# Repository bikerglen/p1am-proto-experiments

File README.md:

# p1am-proto-experiments
Various board and libraries to fit the Automation Direct P1AM-PROTO enclosure.
Everything here is untested. Use at your own risk. I'll accept pull requests with any corrections or other contributions.

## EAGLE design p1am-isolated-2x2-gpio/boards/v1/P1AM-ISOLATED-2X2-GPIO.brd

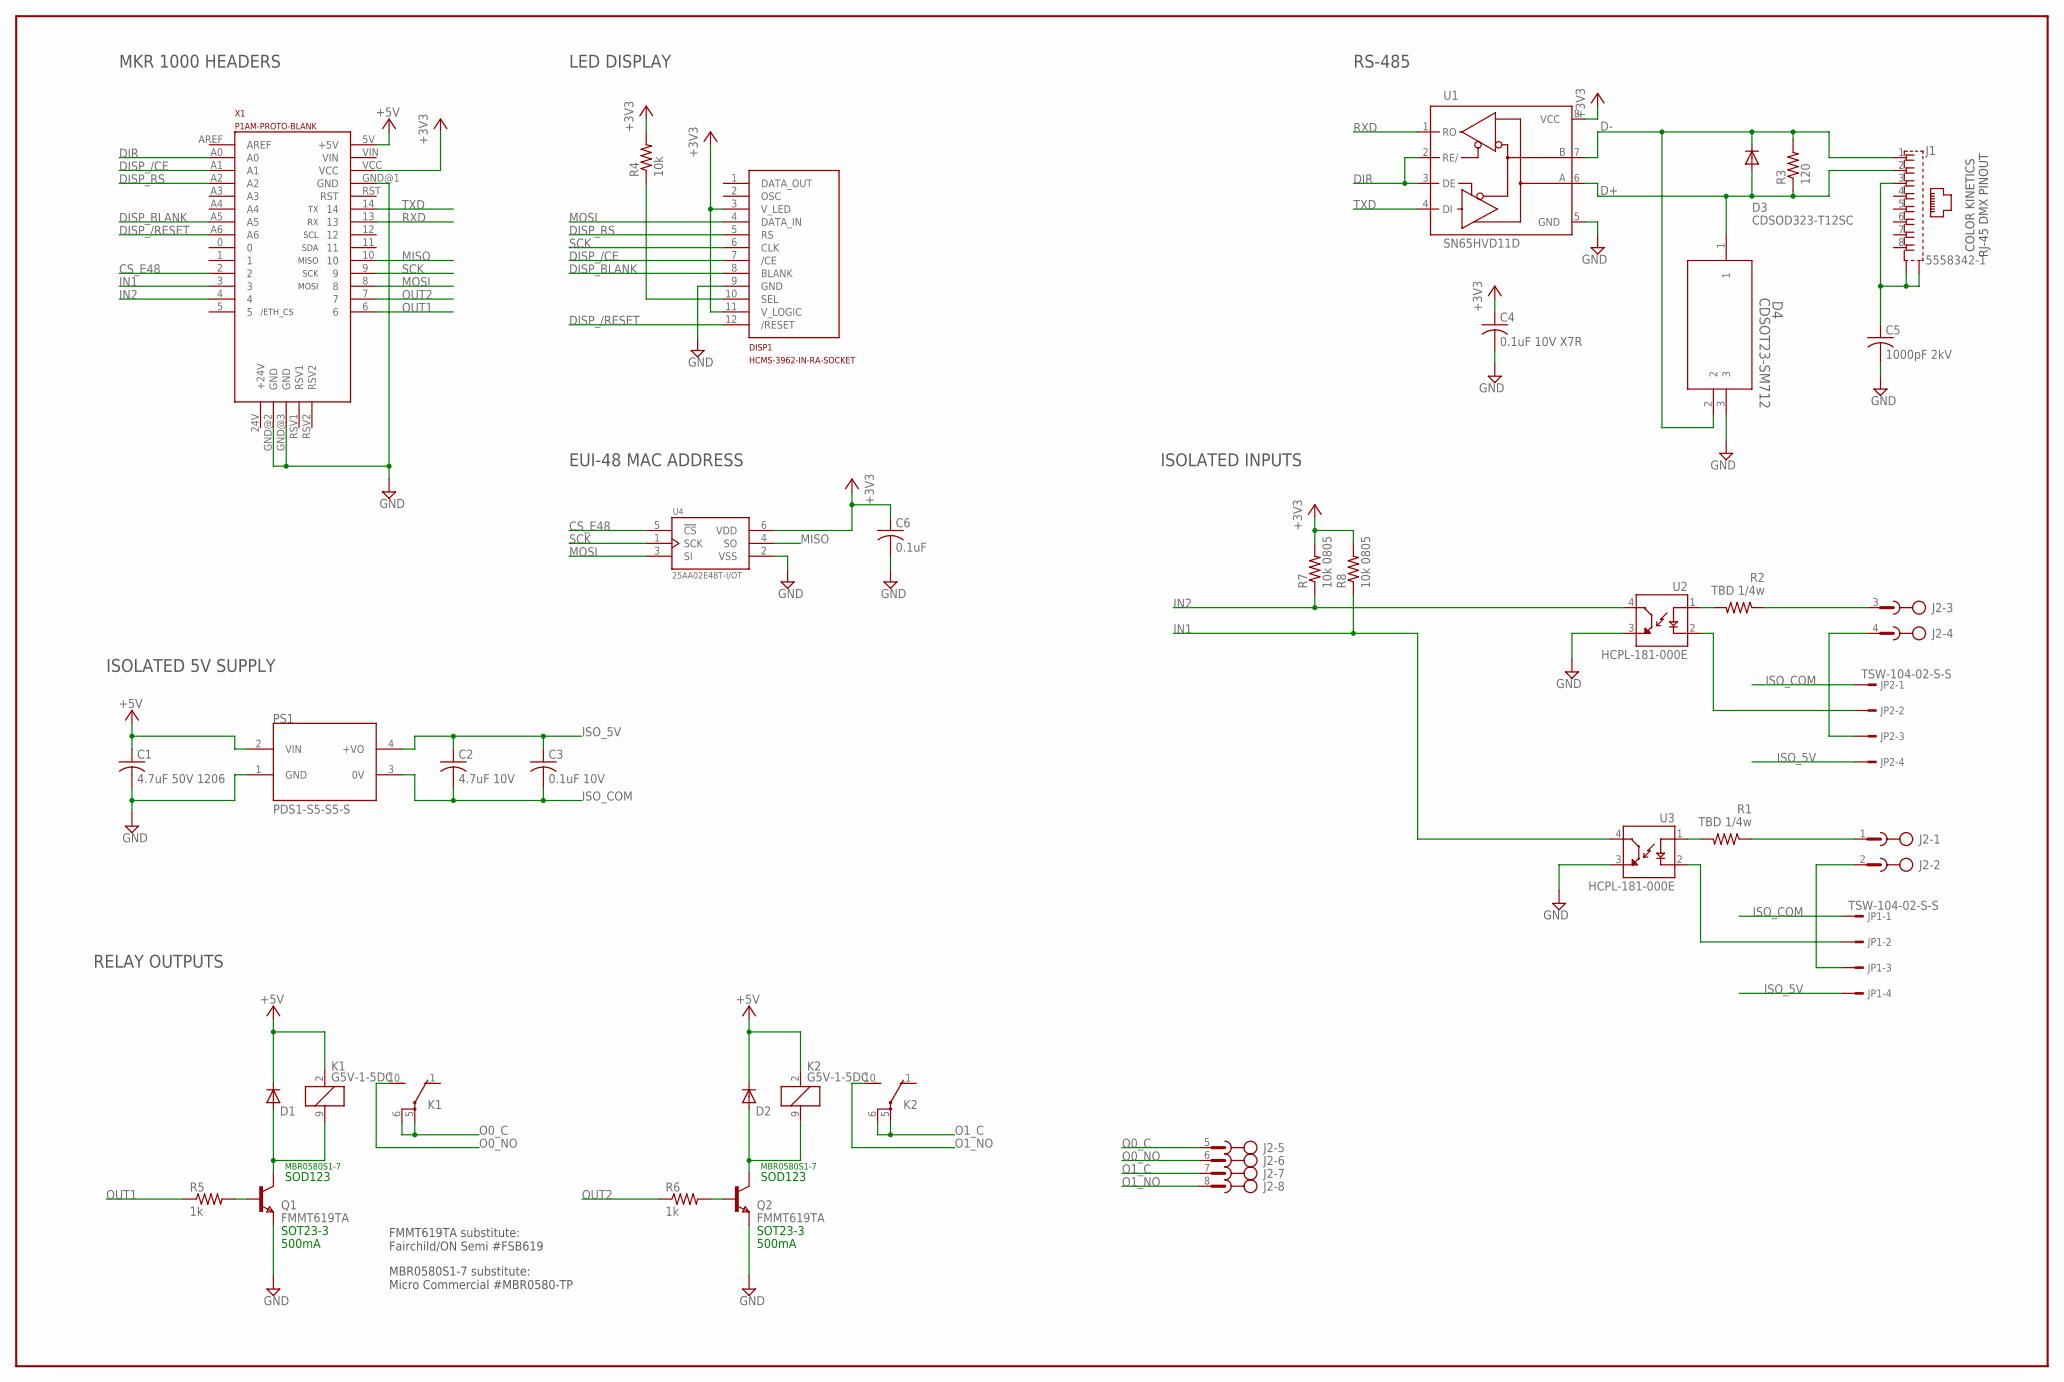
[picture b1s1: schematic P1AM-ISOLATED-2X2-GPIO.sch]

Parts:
C1: 4.7uF 50V 1206; C1206K; MFR_PART_NO C1206C475K5RACTU
C2: 4.7uF 10V; C1206K
C3: 0.1uF 10V; C1206K; MFR_PART_NO C1206C475K5RACTU
C4: 0.1uF 10V X7R; C0805
C5: 1000pF 2kV; C1206K
C6: 0.1uF; C0603
D1, D2: 1N4148W-TP; SOD123; MFR_PART_NO MBR0580S1-7
D3: CDSOD323-T12SC; SOD323-W
D4: CDSOT23-SM712; SOT_SM712
DISP1: HCMS-3962-IN-RA-SOCKET; 299-43-312-11-001000
J1: 5558342-1; TE_5558342-1
J2: PHOENIX-XXXXXXX-TERM-BLOCK-HDR-8POS-90DEG-3.5MM
JP1, JP2: TSW-104-02-S-S
K1, K2: G5V-1-5DC; G5V1; MFR_PART_NO G5V-1-DC5
PS1: PDS1-S5-S5-S; CONV_PDS1-S5-S5-S
Q1, Q2: FMMT619TA; SOT-23; MFR_PART_NO FMMT619TA
R1, R2: TBD 1/4w; R1206
R3: 120; R0805
R4: 10k; R0805
R5, R6: 1k; R1206; MFR_PART_NO CR1206-JW-102ELF
R7, R8: 10k 0805; R0805
U1: SN65HVD11D; SO08
U2, U3: HCPL-181-000E; SOIC254P675X240-4N
U4: 25AA02E48T-I/OT; SOT95P270X145-6N
X1: P1AM-PROTO-BLANK

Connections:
+3V3: C4.1, C6.1, DISP1.3 (V_LED), DISP1.11 (V_LOGIC), R4.2, R7.2, R8.2, U1.8 (VCC), U4.6 (VDD), X1.VCC
+5V: C1.1, D1.C, D2.C, K1.2 (1), K2.2 (1), PS1.2 (VIN), X1.5V (+5V)
CS_E48: U4.5 (!CS), X1.2
D+: D3.A, D4.1, J1.2, R3.1, U1.6 (A)
D-: D3.C, D4.2, J1.1, R3.2, U1.7 (B)
DIR: U1.2 (RE/), U1.3 (DE), X1.A0
DISP_/CE: DISP1.7 (/CE), X1.A1
DISP_/RESET: DISP1.12 (/RESET), X1.A6
DISP_BLANK: DISP1.8 (BLANK), X1.A5
DISP_RS: DISP1.5 (RS), X1.A2
GND: C1.2, C4.2, C5.2, C6.2, D4.3, DISP1.9 (GND), PS1.1 (GND), Q1.2 (E), Q2.2 (E), U1.5 (GND), U2.3 (EMITTER), U3.3 (EMITTER), U4.2 (VSS), X1.GND@1 (GND), X1.GND@2 (GND), X1.GND@3 (GND)
IN1: R8.1, U3.4 (COLLECTOR), X1.3
IN2: R7.1, U2.4 (COLLECTOR), X1.4
ISO_5V: C2.1, C3.1, JP1.4, JP2.4, PS1.4 (+VO)
ISO_COM: C2.2, C3.2, JP1.1, JP2.1, PS1.3 (0V)
MISO: U4.4 (SO), X1.10
MOSI: DISP1.4 (DATA_IN), U4.3 (SI), X1.8
unnamed: R1.2, U3.1 (ANODE)
unnamed: JP1.2, U3.2 (CATHODE)
unnamed: Q2.3 (B), R6.2
unnamed: D2.A, K2.9 (2), Q2.1 (C)
unnamed: J2.3, R2.1
unnamed: J2.2, JP1.3
unnamed: R2.2, U2.1 (ANODE)
unnamed: JP2.2, U2.2 (CATHODE)
unnamed: J2.1, R1.1
unnamed: J2.4, JP2.3
unnamed: C5.1, J1.3, J1.SH1 (S1), J1.SH2 (S2)
unnamed: DISP1.10 (SEL), R4.1
unnamed: Q1.3 (B), R5.2
unnamed: D1.A, K1.9 (2), Q1.1 (C)
O0_C: J2.5, K1.5, K1.6
O0_NO: J2.6, K1.10 (S)
O1_C: J2.7, K2.5, K2.6
O1_NO: J2.8, K2.10 (S)
OUT1: R5.1, X1.6
OUT2: R6.1, X1.7
RXD: U1.1 (RO), X1.13
SCK: DISP1.6 (CLK), U4.1 (SCK), X1.9
TXD: U1.4 (DI), X1.14

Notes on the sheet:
SOD123
SOT23-3
500mA
MBR0580S1-7
FMMT619TA substitute: Fairchild/ON Semi #FSB619
MBR0580S1-7 substitute: Micro Commercial #MBR0580-TP
COLOR KINETICS RJ-45 DMX PINOUT
SCL
SDA
MISO
MOSI
SCK
/ETH_CS
RS-485
ISOLATED INPUTS
RELAY OUTPUTS
MKR 1000 HEADERS
LED DISPLAY
EUI-48 MAC ADDRESS
ISOLATED 5V SUPPLY

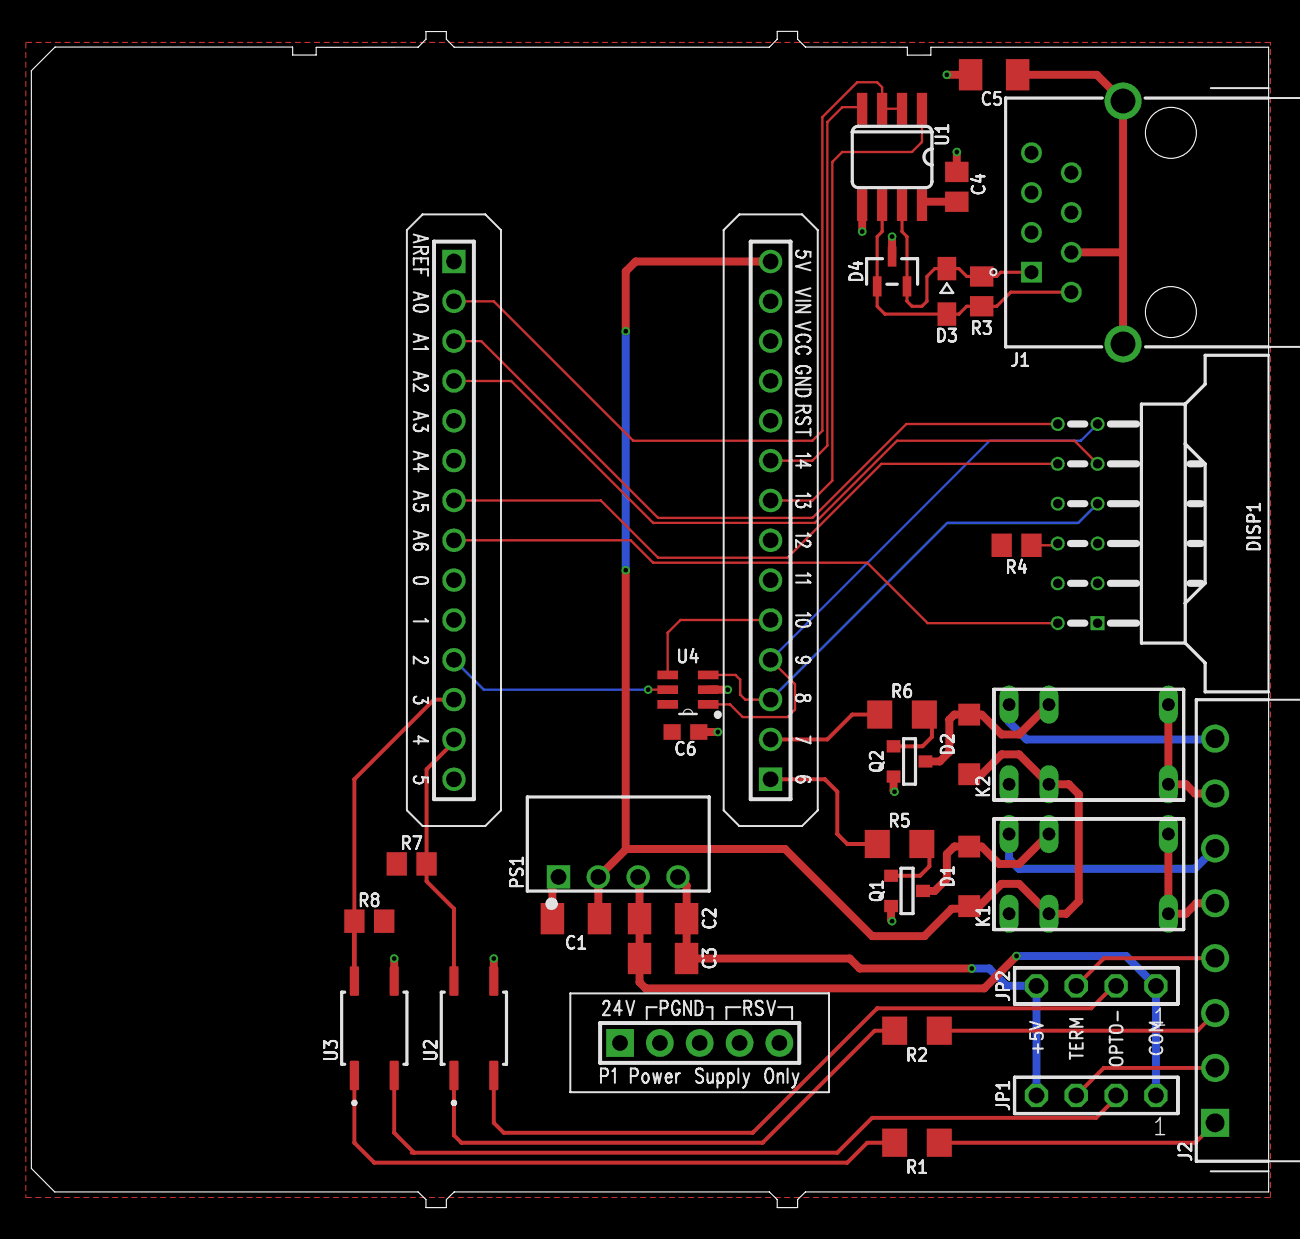
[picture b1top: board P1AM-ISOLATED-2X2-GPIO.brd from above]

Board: 2 copper layers, 78.9 x 75.0 mm, 33 parts (0 on the bottom side), 40 nets.

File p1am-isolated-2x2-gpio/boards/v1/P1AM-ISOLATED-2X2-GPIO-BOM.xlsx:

Qty | Ref | Description | Package | Mfr | Mfr Part # | Supplier | Supplier Part #
2 | C1, C2 | CAP CER 4.7UF 16V X7R 1206 | 1206 | Kemet | C1206C475K4RACTU | Digi-Key | 399-3524-1-ND
1 | C3 | CAP CER 0.1UF 16V X7R 1206 | 1206 | Kemet | C1206C104K4RACTU | Digi-Key | 399-9305-1-ND
1 | C4 | CAP CER 0.1UF 10V X7R 0805 | 0805 | Kemet | C0805C104K8RACTU | Digi-Key | 399-7999-1-ND
1 | C5 | CAP CER 1000pF 2KV 10% X7R SMD 1206 | 1206 | Johanson Dielectrics | 202R18W102KV4E | Digi-Key | 709-1036-1-ND
1 | C6 | CAP CER 0.1UF 50V X7R 0603 | 0603 | Kemet | C0603C104K5RACTU | Digi-Key | 399-5089-1-ND
2 | D1, D2 | DIODE GEN PURP 100V 150MA SOD123 | SOD123 | Micro Commercial Co | 1N4148W-TP | Digi-Key | 1N4148WTPMSCT-ND
1 | D3 | TVS DIODE 12V 29.5V SOD323 | SOD323 | Bourns Inc. | CDSOD323-T12SC | Digi-Key | CDSOD323-T12SCCT-ND
1 | D4 | TVS DIODE 7V/12V 14V/26V SOT23-3 | SOT23 | Bourns Inc. | CDSOT23-SM712 | Digi-Key | CDSOT23-SM712CT-ND
1 | DISP1-DISPLAY | LED DISPLAY 5X7 4CHAR 5MM RED | --- | Broadcom | HCMS-3962 | Digi-Key | 516-3920-ND
1 | DISP1-SOCKET | CONN IC DIP SOCKET 12POS GOLD | --- | Mill-Max | 299-43-312-11-001000 | Digi-Key | ED90160-ND
1 | J1 | CONN MOD JACK 8P8C R/A SHIELDED | 8P8C | TE Connectivity | 5558342-1 | Digi-Key | A31466-ND
1 | J2-HEADER | TERM BLOCK HDR 8POS 90DEG 3.5MM | --- | Würth Elektronik | 691322110008 | Digi-Key | 732-2774-ND
1 | J2-PLUG | TERM BLOCK PLUG 8POS STR 3.5MM | --- | Würth Elektronik | 691361100008 | Digi-Key | 732-2756-ND
2 | JP1, JP2 | CONN HEADER VERT 4POS 2.54MM | --- | Samtec | TSW-104-07-G-S | Digi-Key | SAM1029-04-ND
2 | K1, K2 | RELAY GEN PURPOSE SPDT 1A 5VDC | --- | Omron | G5V-1-DC5 | Digi-Key | Z773-ND
1 | PS1 | DC DC CONVERTER 5V 1W | --- | Cui | PDS1-S5-S5-S | Digi-Key | 102-2758-ND
2 | Q1, Q2 | TRANS NPN 50V 2A SOT23-3 | --- | Diodes Incorporated | FMMT619TA | Digi-Key | FMMT619CT-ND
2 | R1, R2 | RES SMD 750 OHM 5% 1/4W 1206 | 1206 | Panasonic | ERJ-8GEYJ751V | Digi-Key | P750ECT-ND
1 | R3 | RES SMD 120 OHM 5% 1/8W 0805 | 0805 | Panasonic | ERJ-6GEYJ121V | Digi-Key | P120ACT-ND
3 | R4, R7, R8 | RES SMD 10K OHM 5% 1/8W 0805 | 0805 | Panasonic | ERJ-6GEYJ103V | Digi-Key | P10KACT-ND
2 | R5, R6 | RES SMD 1K OHM 5% 1/4W 1206 | 1206 | Panasonic | ERJ-8GEYJ102V | Digi-Key | P1.0KECT-ND
1 | U1 | IC TRANSCEIVER HALF 1/1 8SOIC | --- | Texas Instruments | SN65HVD11DR | Digi-Key | 296-31717-1-ND
2 | U2,U3 | OPTOISO 3.75KV TRANSISTOR 4SOIC | --- | Broadcom | HCPL-181-000E | Digi-Key | 516-1646-1-ND
1 | U4 | IC EEPROM 2K SPI 10MHZ SOT23-6 | --- | Microchip | 25AA02E48T-I/OT | Digi-Key | 25AA02E48T-I/OTCT-ND
1 | X1 | P1AM PROTOTYPE HOUSING | --- | Automation Direct | P1AM-PROTO | Automation Direct | P1AM-PROTO

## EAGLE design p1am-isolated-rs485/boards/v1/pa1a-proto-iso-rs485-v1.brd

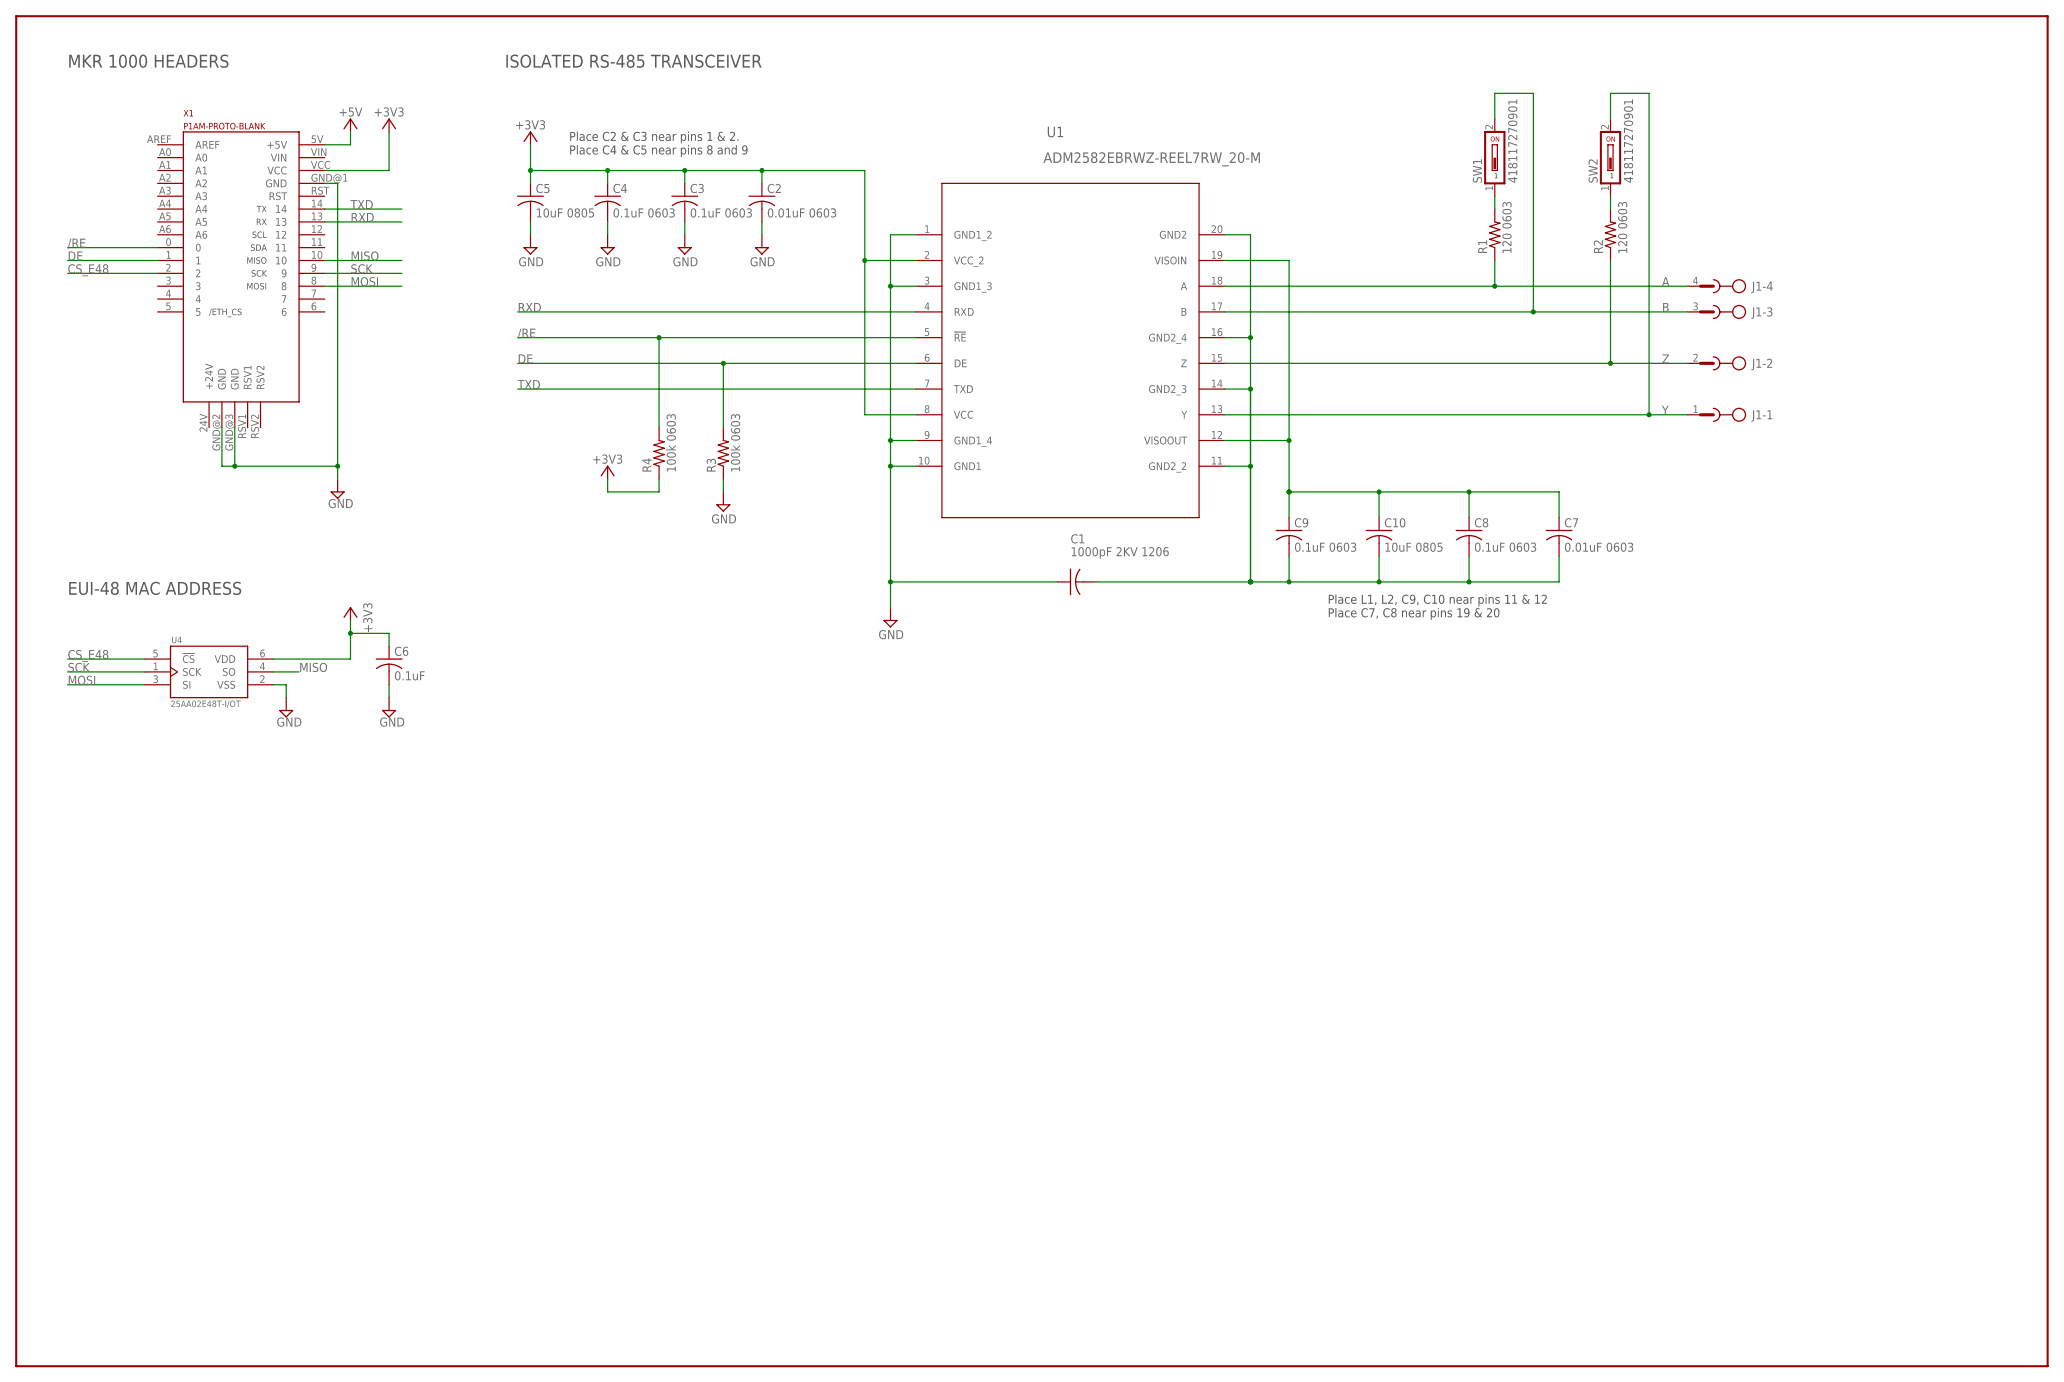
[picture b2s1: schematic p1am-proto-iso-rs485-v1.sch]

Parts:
C1: 1000pF 2KV 1206; C1206K
C2, C7: 0.01uF 0603; C0603K
C3, C4, C8, C9: 0.1uF 0603; C0603K
C5, C10: 10uF 0805; C0805K
C6: 0.1uF; C0603
J1: PHOENIX-XXXXXXX-TERM-BLOCK-HDR-4POS-90DEG-3.5MM
R1, R2: 120 0603; R0603
R3, R4: 100k 0603; R0603
SW1, SW2: 418117270901; DIP-01-PTH
U1: ADM2582EBRWZ-REEL7RW_20-M; RW_20-M
U4: 25AA02E48T-I/OT; SOT95P270X145-6N
X1: P1AM-PROTO-BLANK

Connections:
+3V3: C2.1, C3.1, C4.1, C5.1, C6.1, R4.1, U1.2 (VCC_2), U1.8 (VCC), U4.6 (VDD), X1.VCC
+5V: X1.5V (+5V)
/RE: R4.2, U1.5 (!RE), X1.0
A: J1.4, R1.1, U1.18 (A)
B: J1.3, SW1.2, U1.17 (B)
CS_E48: U4.5 (!CS), X1.2
DE: R3.2, U1.6 (DE), X1.1
GND: C1.1, C2.2, C3.2, C4.2, C5.2, C6.2, R3.1, U1.1 (GND1_2), U1.3 (GND1_3), U1.9 (GND1_4), U1.10 (GND1), U4.2 (VSS), X1.GND@1 (GND), X1.GND@2 (GND), X1.GND@3 (GND)
ISOGND: C1.2, C7.2, C8.2, C9.2, C10.2, U1.11 (GND2_2), U1.14 (GND2_3), U1.16 (GND2_4), U1.20 (GND2)
ISOVCC: C7.1, C8.1, C9.1, C10.1, U1.12 (VISOOUT), U1.19 (VISOIN)
MISO: U4.4 (SO), X1.10
MOSI: U4.3 (SI), X1.8
unnamed: R1.2, SW1.1
unnamed: R2.2, SW2.1
RXD: U1.4 (RXD), X1.13
SCK: U4.1 (SCK), X1.9
TXD: U1.7 (TXD), X1.14
Y: J1.1, SW2.2, U1.13 (Y)
Z: J1.2, R2.1, U1.15 (Z)

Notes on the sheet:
SCL
SDA
MISO
MOSI
SCK
/ETH_CS
MKR 1000 HEADERS
EUI-48 MAC ADDRESS
ISOLATED RS-485 TRANSCEIVER
Place C2 & C3 near pins 1 & 2. Place C4 & C5 near pins 8 and 9
Place L1, L2, C9, C10 near pins 11 & 12 Place C7, C8 near pins 19 & 20

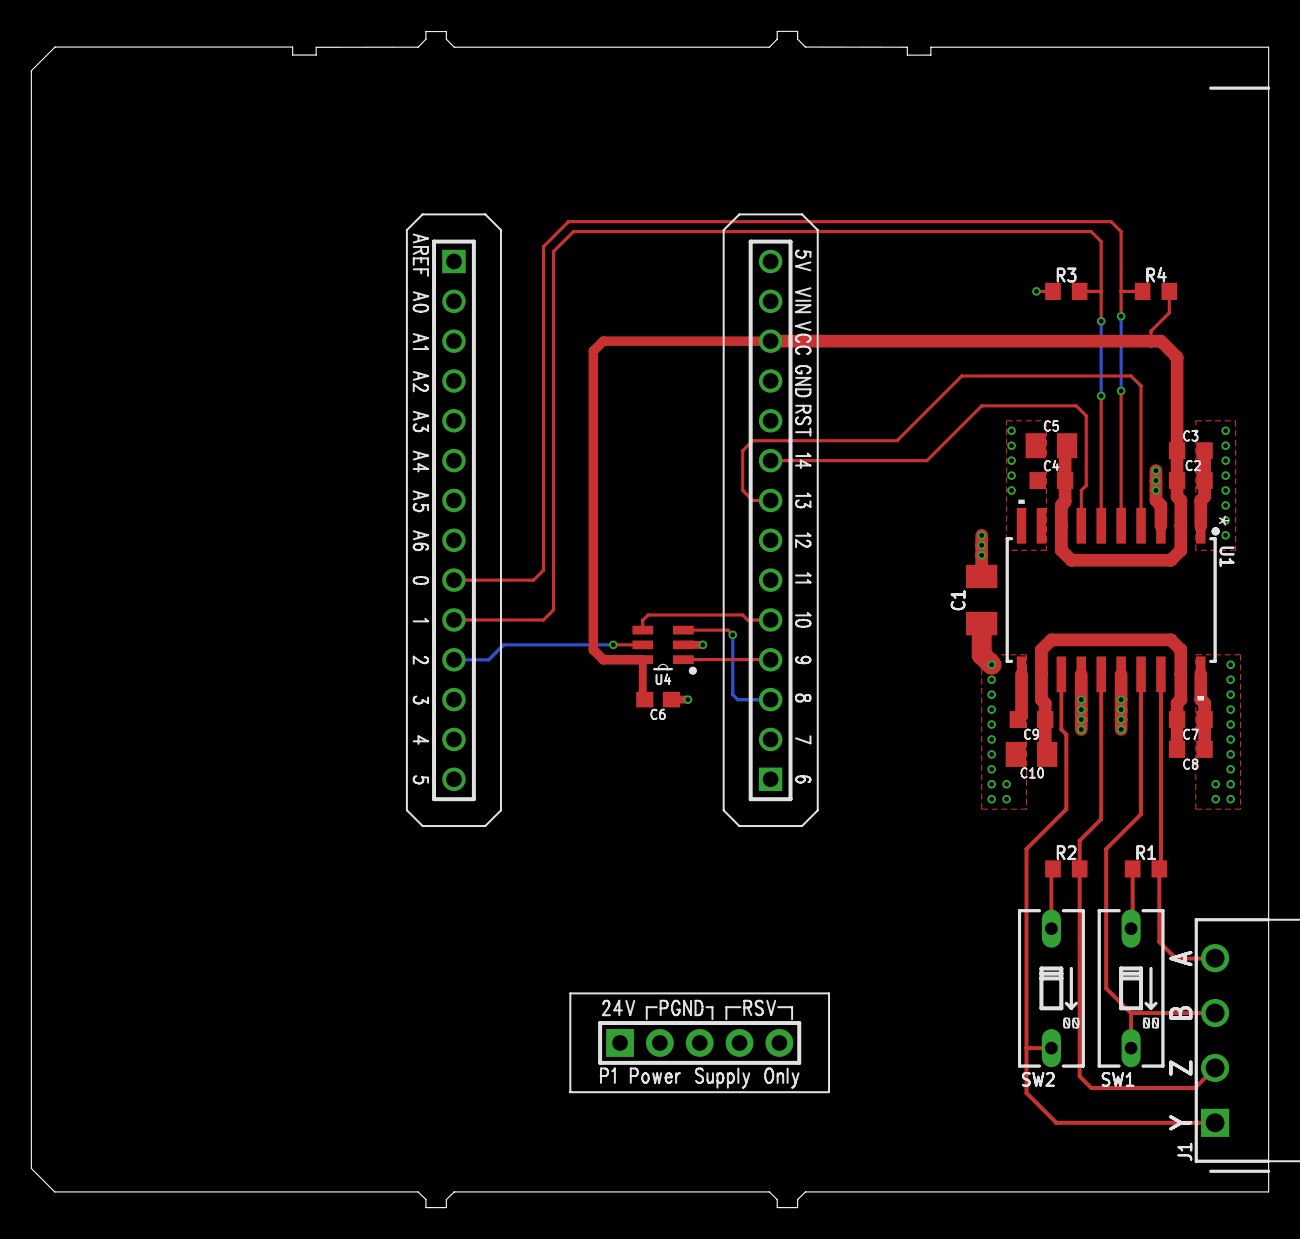
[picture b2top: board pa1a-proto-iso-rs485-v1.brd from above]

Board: 2 copper layers, 78.9 x 75.0 mm, 20 parts (0 on the bottom side), 18 nets.

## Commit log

2020-03-04 initial checkin
2020-03-04 moved library to eagle subdirectory
2020-03-04 Create LICENSE
2020-03-09 made board outline an unbroken continous line
2020-03-22 added schematic, board, and bom
2020-03-22 add hardware test and garage door sketches
2020-03-25 initial checkin of isolated RS-485 board
2020-04-04 fixed board names
2020-04-04 added sketch
2020-04-05 added example application sender and receiver sketches

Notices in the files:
parts and their libraries:
ADM2582EBRWZ-REEL7: COPYRIGHT: Copyright (C) 2018 Accelerated Designs. All rights reserved
